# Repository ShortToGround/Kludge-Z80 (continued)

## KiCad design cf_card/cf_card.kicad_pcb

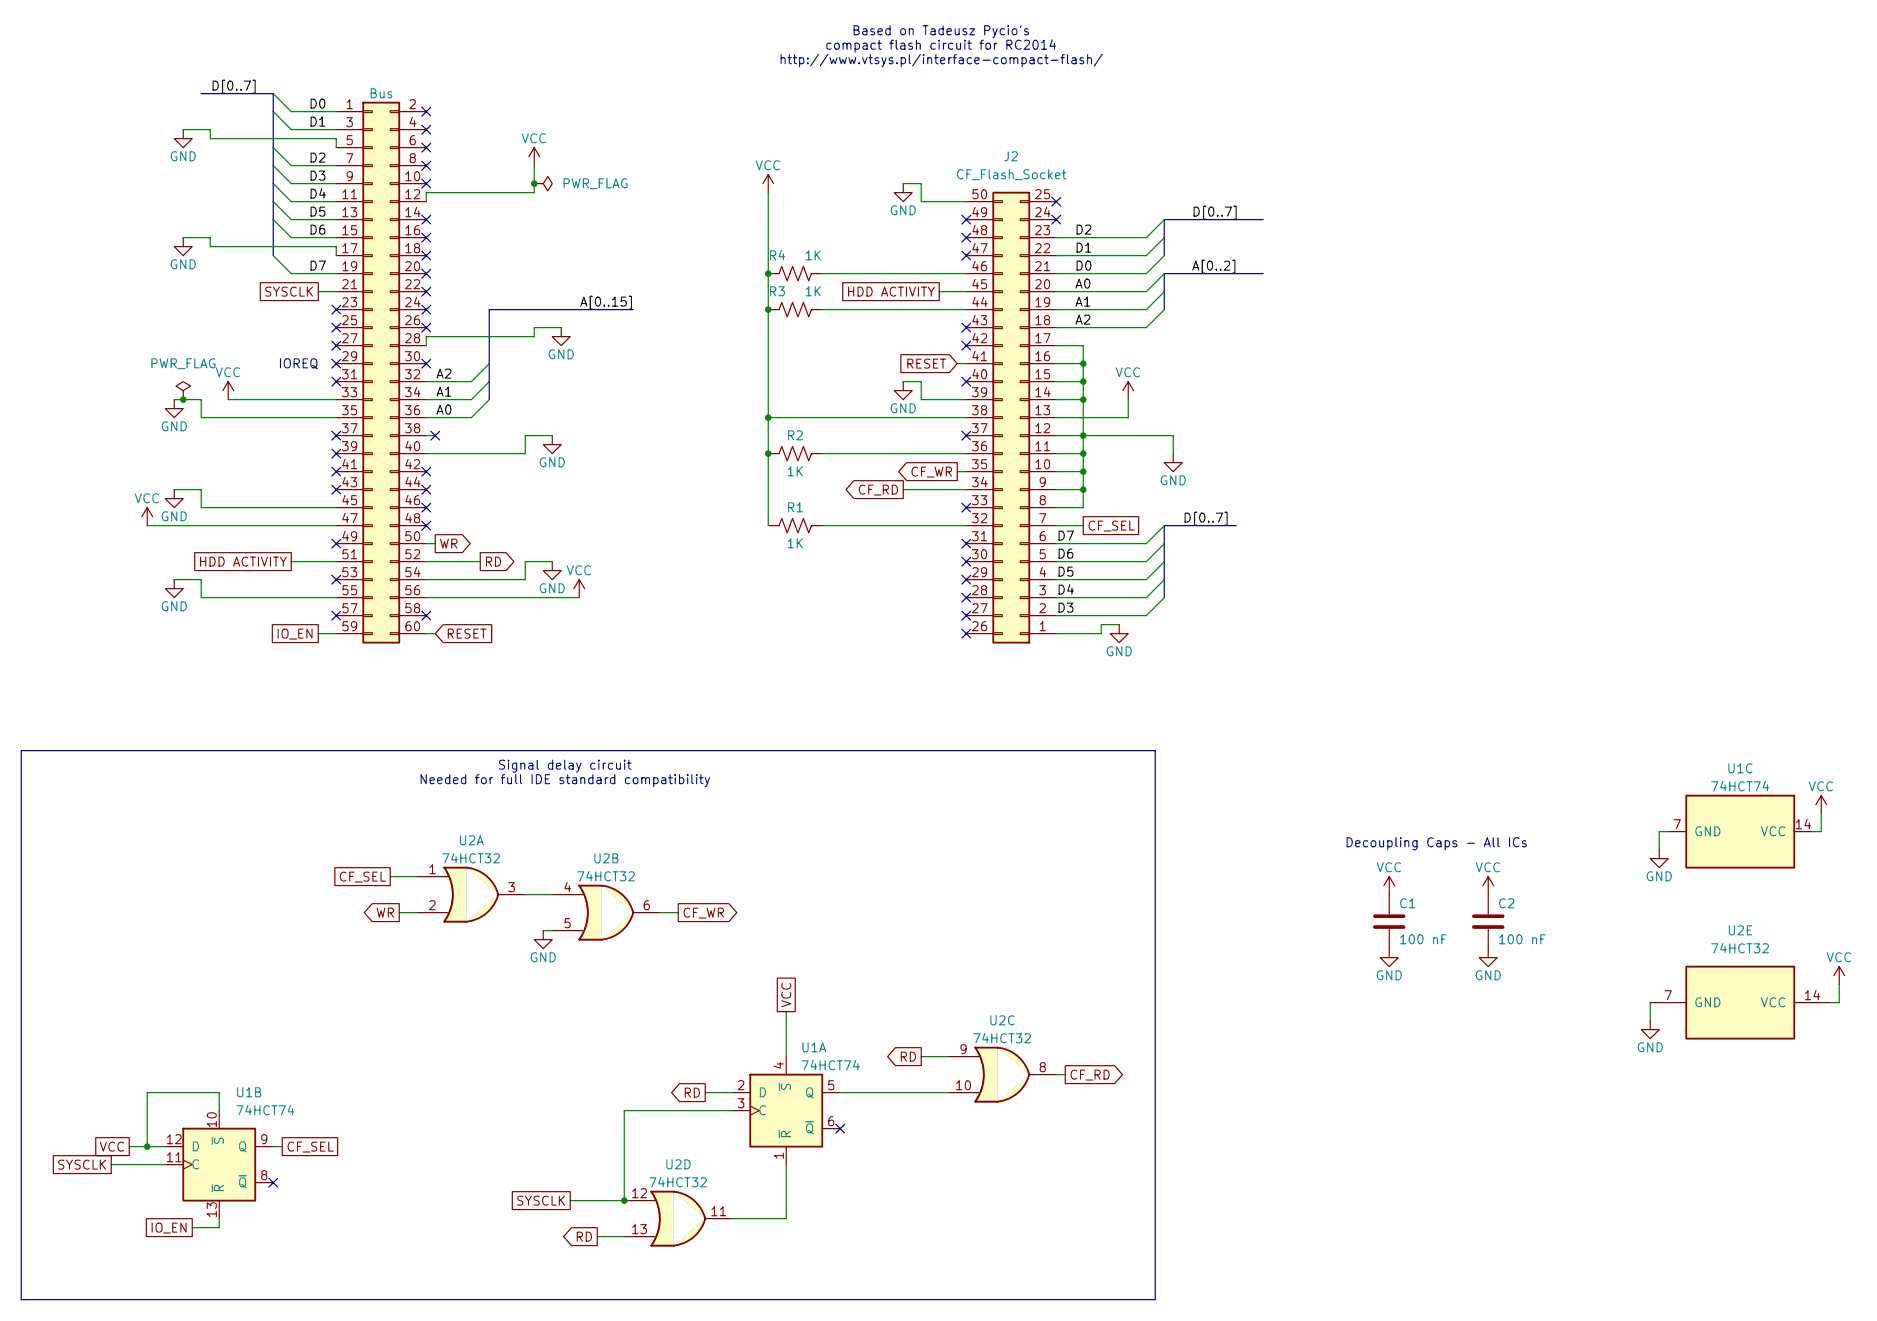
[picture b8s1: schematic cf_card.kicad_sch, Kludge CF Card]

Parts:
C1, C2: 100 nF; C_Disc_D3.0mm_W1.6mm_P2.54mm
J1: Bus; PinHeader_2x30_P2.54mm_Vertical
J2: CF_Flash_Socket; N7E50Q516RB40
R1, R2, R3, R4: 1K; R_Axial_DIN0207_L6.3mm_D2.5mm_P10.16mm_Horizontal
U1: 74HCT74; DIP-14_W7.62mm
U2: 74HCT32; DIP-14_W7.62mm

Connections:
/A0: J1.36, J2.20
/A1: J1.34, J2.19
/A2: J1.32, J2.18
/D0: J1.1, J2.21
/D1: J1.3, J2.22
/D2: J1.7, J2.23
/D3: J1.9, J2.2
/D4: J1.11, J2.3
/D5: J1.13, J2.4
/D6: J1.15, J2.5
/D7: J1.19, J2.6
CF_RD: J2.34, U2.8
CF_SEL: J2.7, U1.9 (Q), U2.1
CF_WR: J2.35, U2.6
GND: C1.2, C2.2, J1.5, J1.17, J1.28, J1.35, J1.40, J1.45, J1.54, J1.55, J2.1, J2.8, J2.9, J2.10, J2.11, J2.12, J2.14, J2.15, J2.16, J2.17, J2.39, J2.50, U1.7 (GND), U2.5, U2.7 (GND)
HDD ACTIVITY: J1.51, J2.45
IO_EN: J1.59, U1.13 (~R)
unnamed: J2.32, R1.2
unnamed: J2.36, R2.2
unnamed: J2.44, R3.2
unnamed: J2.46, R4.2
unnamed: U1.5 (Q), U2.10
unnamed: U1.1 (~R), U2.11
unnamed: U2.3, U2.4
RD: J1.52, U1.2 (D), U2.9, U2.13
RESET: J1.60, J2.41
SYSCLK: J1.21, U1.3 (C), U1.11 (C), U2.12
VCC: C1.1, C2.1, J1.12, J1.33, J1.47, J1.56, J2.13, J2.38, R1.1, R2.1, R3.1, R4.1, U1.4 (~S), U1.10 (~S), U1.12 (D), U1.14 (VCC), U2.14 (VCC)
WR: J1.50, U2.2

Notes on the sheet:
IOREQ
Signal delay circuit Needed for full IDE standard compatibility
Decoupling Caps - All ICs
Based on Tadeusz Pycio's compact flash circuit for RC2014 http://www.vtsys.pl/interface-compact-flash/

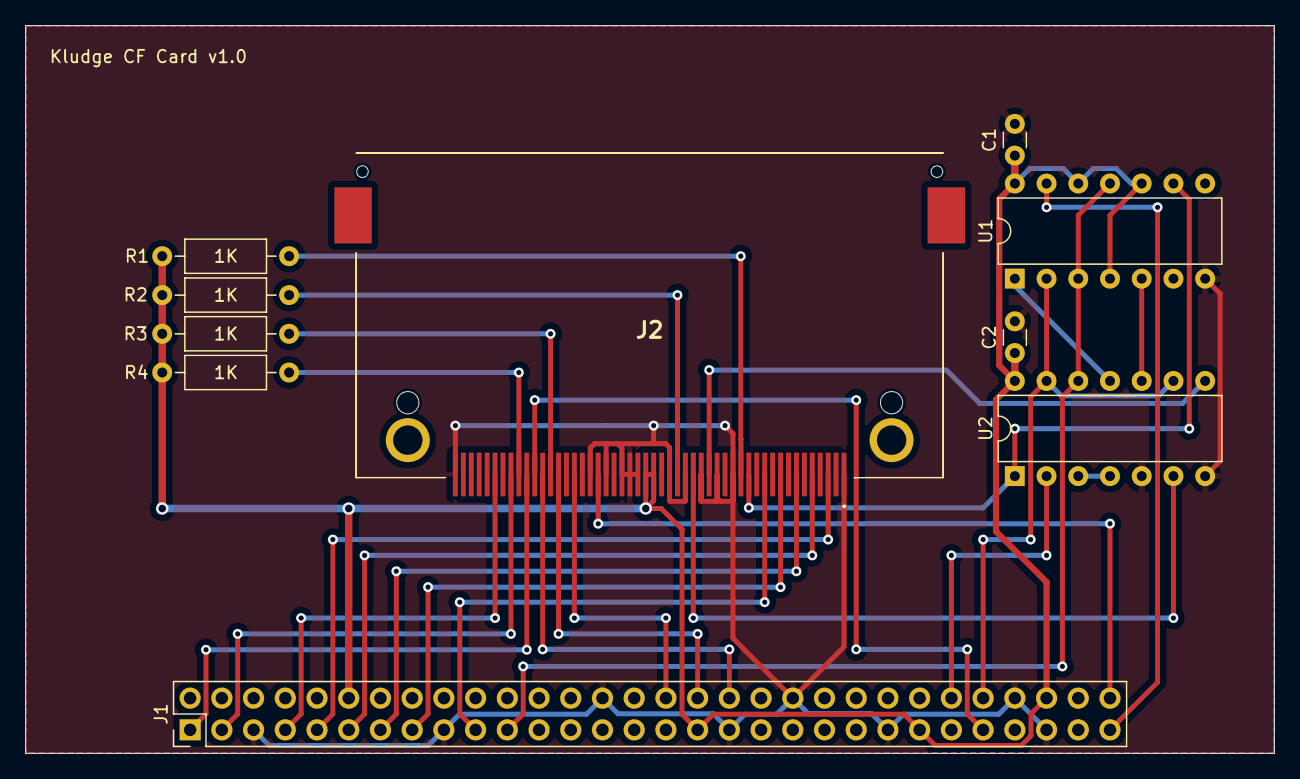
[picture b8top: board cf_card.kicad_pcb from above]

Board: 2 copper layers, 100.0 x 58.3 mm, 10 parts (0 on the bottom side), 29 nets.

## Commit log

2023-09-11 added color pcb pdf file
2023-09-11 changed signal traces from 0.25mm to 0.3mm and moved a few traces arround to accommodate the new size
2023-09-11 Added active-high reset to bus
2023-09-12 Changed Z80 input pull-up resistors to lower values to account for transition time at 10Mhz
2023-09-13 exported pcb so it is easier to see
2023-09-21 Changed the bus hardware to 2.54mm header and cleaned up the CPU card PCB layout
2023-09-21 Changed CPU board to nominal 20MHz with the option to adjust using the 2x5 header.
2023-09-21 added 3d models for some parts
2023-09-21 removed old PDFs and uploaded new ones
2023-10-20 Mostly finished with cpu_card, added early prototypes of backplane and protoboard cards. Also added the libraries used for this project
2023-10-20 Updated cpu_card PDFs to match changes.
2024-12-27 backplane initial commit
2024-12-27 added picture of backplane
2024-12-27 added backplane schematic pdf
2024-12-30 Memory card initial commit
2024-12-30 Sound card initial commit
2024-12-30 Removed unneeded files from sound_card dir
2024-12-30 Added pdf of sound_card schematic
2024-12-30 Added address map to schematic and pcb silkscreen
2024-12-30 updated sound_card pdf to reflect new notes on schematic
2024-12-30 Fixed mislabeled title on schematic
2024-12-30 cpu_card initial commit
2024-12-30 cf_card initial commit
2024-12-30 filled in zones
2024-12-30 IDE Card initial commit
2024-12-30 protoboard_card initial commit
2024-12-30 Updated README to reflect changes to the protoboard card
2024-12-30 network_card initial commit
2024-12-30 ps2_card initial commit
2024-12-30 rtc_card initial commit
2024-12-30 serial_card initial commit
2024-12-30 video_card initial commit
2025-01-08 Added missing decoupling capacitor to U6. Also reorganzied all decoupling capacitor's reference value to make it flow better on the PCB
2025-01-08 Fixed capacitor silkscreen placement and overlap issues
2025-01-08 Added missing decoupling capacitor for U6
2025-01-14 Fixed mirrored PS/2 port footprint.
2025-01-15 Replaced 74xx04's with 74xx06's in order for the ps/2 device to be able to properly send data/clock
2025-01-20 Fixed misplacement of network module footprint. Added second footprint on edge of PCB for IDC connector
2025-01-20 Swapped out '4245' on the INT signal to a more simple transistor circuit
